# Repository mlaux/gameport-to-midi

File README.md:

# Game port to MIDI adapter

This adapter allows the connection of MIDI devices to the 'game port' or joystick port found on old sound cards. It's similar to the reference circuit given in the MIDI specification, but obsolete parts have been replaced with modern equivalents.

KiCad schematic and layout files are provided, as well as three custom footprints (the DIN-5 MIDI connector, the DA-15 game port connector, and the MIDI logo).

<table>
    <tr>
        <td>
            
        </td>
        <td>
            
        </td>
    </tr>
</table>

## Bill of Materials

<table>
    <thead>
        <tr>
            <th>Reference</th>
            <th>Value</th>
            <th>Mouser P/N</th>
        </tr>
    </thead>
    <tbody>
        <tr>
            <td>J1</td>
            <td>DA-15 PCB mount connector, pin</td>
            <td>636-182-015-113R531</td>
        </tr>
        <tr>
            <td>J2-J3</td>
            <td>DIN-5 180° socket</td>
            <td>502-57PC5F</td>
        </tr>
        <tr>
            <td>U1</td>
            <td>74HCT04 hex inverter</td>
            <td>595-SN74HCT04N</td>
        </tr>
        <tr>
            <td>U2</td>
            <td>H11L1M optoisolator</td>
            <td>512-H11L1M</td>
        </tr>
        <tr>
            <td>R1-R4</td>
            <td>270 ohm, 1/4 watt</td>
            <td></td>
        </tr>
        <tr>
            <td>C1</td>
            <td>0.1 μF</td>
            <td></td>
        </tr>
        <tr>
            <td>D1</td>
            <td>Small signal, 1N4148</td>
            <td></td>
        </tr>
    </tbody>
</table>

I also recommend IC sockets because they're cheap and look nice.

## License

GNU General Public License v3

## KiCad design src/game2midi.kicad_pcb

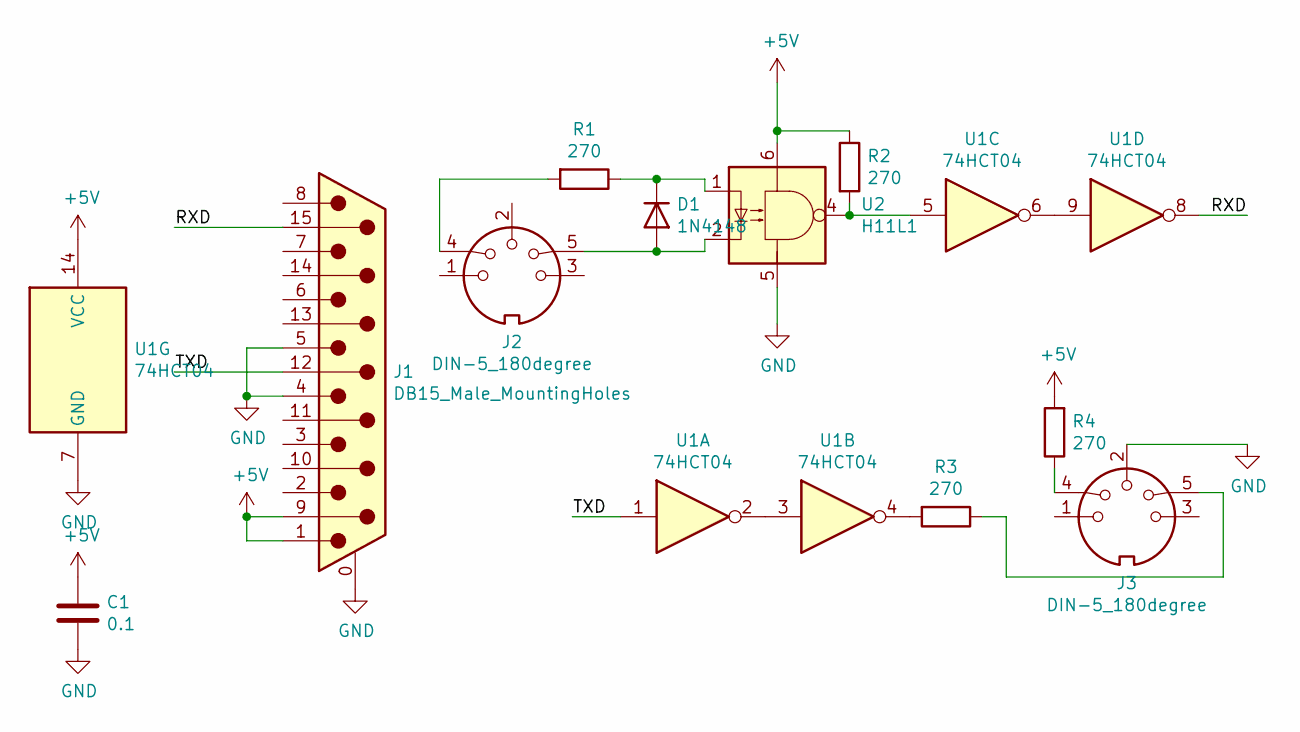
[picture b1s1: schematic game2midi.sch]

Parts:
C1: 0.1; C_Disc_D3.0mm_W1.6mm_P2.50mm
D1: 1N4148; D_DO-35_SOD27_P7.62mm_Horizontal
J1: DB15_Male_MountingHoles; 182-YYY-113RYY1
J2, J3: DIN-5_180degree; 57PC5F
R1, R2, R3, R4: 270; R_Axial_DIN0204_L3.6mm_D1.6mm_P7.62mm_Horizontal
U1: 74HCT04; DIP-14_W7.62mm_Socket_LongPads
U2: H11L1; DIP-6_W7.62mm_Socket_LongPads

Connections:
+5V: C1.1, J1.1, J1.9, R2.1, R4.2, U1.14 (VCC), U2.6
/RXD: J1.15, U1.8
/TXD: J1.12, U1.1
GND: C1.2, J1.0 (PAD), J1.4, J1.5, J3.2, U1.7 (GND), U2.5
unnamed: D1.1 (K), R1.1, U2.1
unnamed: D1.2 (A), J2.5, U2.2
unnamed: J2.4, R1.2
unnamed: J3.4, R4.1
unnamed: J3.5, R3.1
unnamed: R2.2, U1.5, U2.4
unnamed: R3.2, U1.4
unnamed: U1.2, U1.3
unnamed: U1.6, U1.9

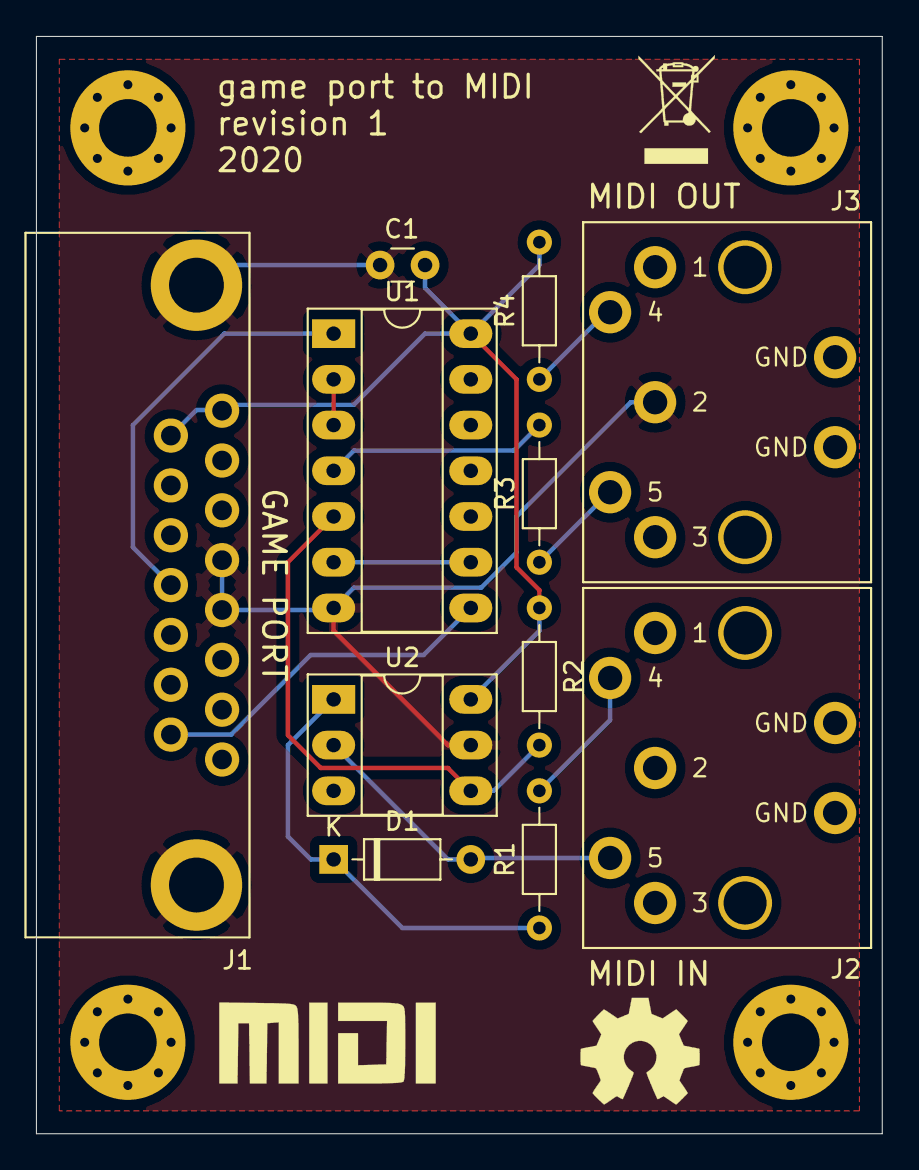
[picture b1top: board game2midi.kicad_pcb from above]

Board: 2 copper layers, 47.0 x 61.0 mm, 11 parts (0 on the bottom side), 13 nets.

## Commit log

2020-11-29 add README
2020-11-29 add BoM
2020-11-29 add GPLv3
